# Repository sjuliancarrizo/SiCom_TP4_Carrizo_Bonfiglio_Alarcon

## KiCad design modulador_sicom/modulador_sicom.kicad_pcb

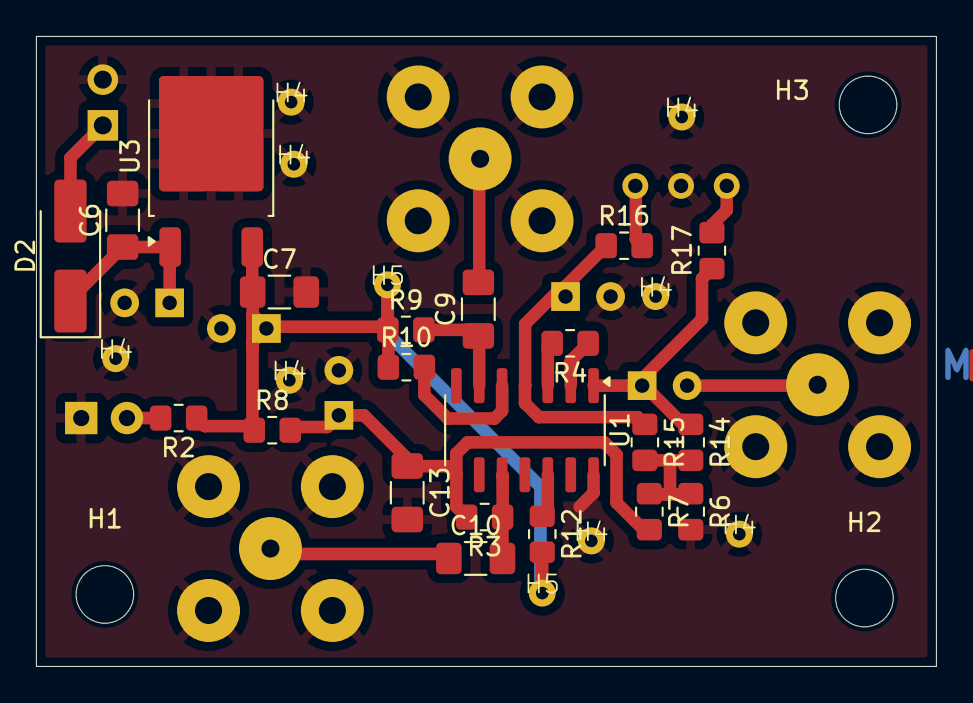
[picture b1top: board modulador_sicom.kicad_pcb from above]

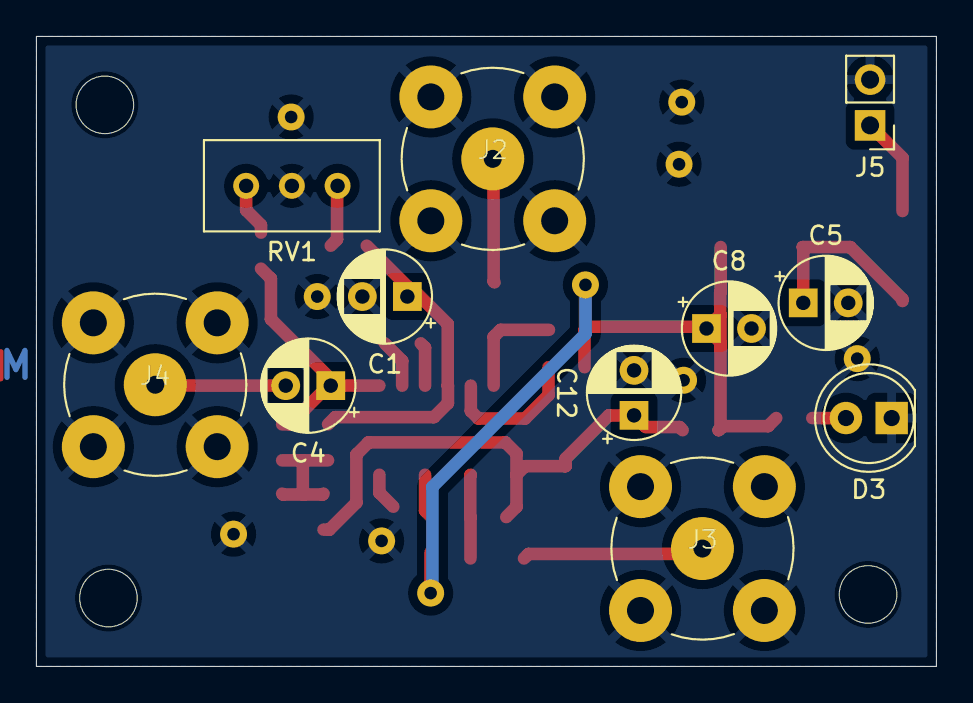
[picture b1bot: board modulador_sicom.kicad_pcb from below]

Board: 2 copper layers, 50.0 x 35.0 mm, 45 parts (11 on the bottom side), 20 nets.

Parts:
C1, C12: 25u; CP_Radial_D5.0mm_P2.50mm
C4, C5, C8: 10u; CP_Radial_D5.0mm_P2.50mm
C6, C7, C9, C10, C13: 100n; L_1206_3216Metric_Pad1.42x1.75mm_HandSolder
D2: 1N4007; D_SMA_Handsoldering
D3: LED; LED_D5.0mm
H1, H2, H3: MountingHole; MountingHole_3.2mm_M3
H4, H4#2, H4#3, H4#4, H4#5, H4#6, H4#7, H4#8, H5, H5#2: Via_0.7x1.5
J2: OUTPUT; BNC_TEConnectivity_413969-2
J3: CARRIER_IN; BNC_TEConnectivity_413969-2
J4: MODULATING; BNC_TEConnectivity_413969-2
J5: POWER; PinHeader_1x02_P2.54mm_Vertical
R2, R4, R6: 1k; R_0805_2012Metric_Pad1.20x1.40mm_HandSolder
R3: 51; R_0805_2012Metric_Pad1.20x1.40mm_HandSolder
R7: 820; R_0805_2012Metric_Pad1.20x1.40mm_HandSolder
R8: 1.3k; R_0805_2012Metric_Pad1.20x1.40mm_HandSolder
R9, R12: 3k; R_0805_2012Metric_Pad1.20x1.40mm_HandSolder
R10, R16, R17: 10k; R_0805_2012Metric_Pad1.20x1.40mm_HandSolder
R14, R15: 100; R_0805_2012Metric_Pad1.20x1.40mm_HandSolder
RV1: 10k; Potentiometer_Bourns_3296W_Vertical
U1: MC1496D; SOIC-14_3.9x8.7mm_P1.27mm
U3: L7812; TO-252-2

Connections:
+12V: C7.1, C8.1, H5.1 (Via), H5#2.1 (Via), R2.1, R8.1, R9.1, R10.1, R12.2, U3.3 (OUT)
/CARRIER: C10.1, J3.1 (In)
/CARRIER_A: C10.2, R3.1, U1.10 (CARRIER_IN)
/MOD: C4.2, J4.1 (In)
/MOD_A: C4.1, R14.1, R17.1, U1.1 (SIG_IN_2)
/OUT: C9.2, J2.1 (In)
/OUT_A: C9.1, R9.2, U1.6 (OUT)
/V_IN: C5.1, C6.1, D2.1 (K), U3.1 (IN)
GND: C1.2, C5.2, C6.2, C7.2, C8.2, C12.2, C13.2, D3.1 (K), H4.1 (Via), H4#2.1 (Via), H4#3.1 (Via), H4#4.1 (Via), H4#5.1 (Via), H4#6.1 (Via), H4#7.1 (Via), H4#8.1 (Via), J2.2 (Ext), J3.2 (Ext), J4.2 (Ext), J5.2, R6.2, RV1.2, U1.14 (VEE), U3.2 (GND)
unnamed: D2.2 (A), J5.1
unnamed: D3.2 (A), R2.2
unnamed: R12.1, U1.12 (OUT)
unnamed: R6.1, R7.1, R14.2, R15.2
unnamed: R16.2, RV1.3
unnamed: R17.2, RV1.1
unnamed: R10.2, U1.5 (BIAS)
unnamed: R4.1, U1.2 (GAIN_ADJ)
unnamed: R4.2, U1.3 (GAIN_ADJ_2)
unnamed: C12.1, C13.1, R3.2, R7.2, R8.2, U1.8 (IN_CARRIER)
unnamed: C1.1, R15.1, R16.1, U1.4 (SIG_IN)

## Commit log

2024-08-13 Create kicad projects.
2024-08-15 Update pcb layout.
2024-08-16 Fix missing connection.
    - Add RP diode.
2024-08-24 Change BNC footprint.
    - Replace vias for holes, so they can have thermal relief.
    - Export fabrication files
2024-08-27 Update latest changes.
